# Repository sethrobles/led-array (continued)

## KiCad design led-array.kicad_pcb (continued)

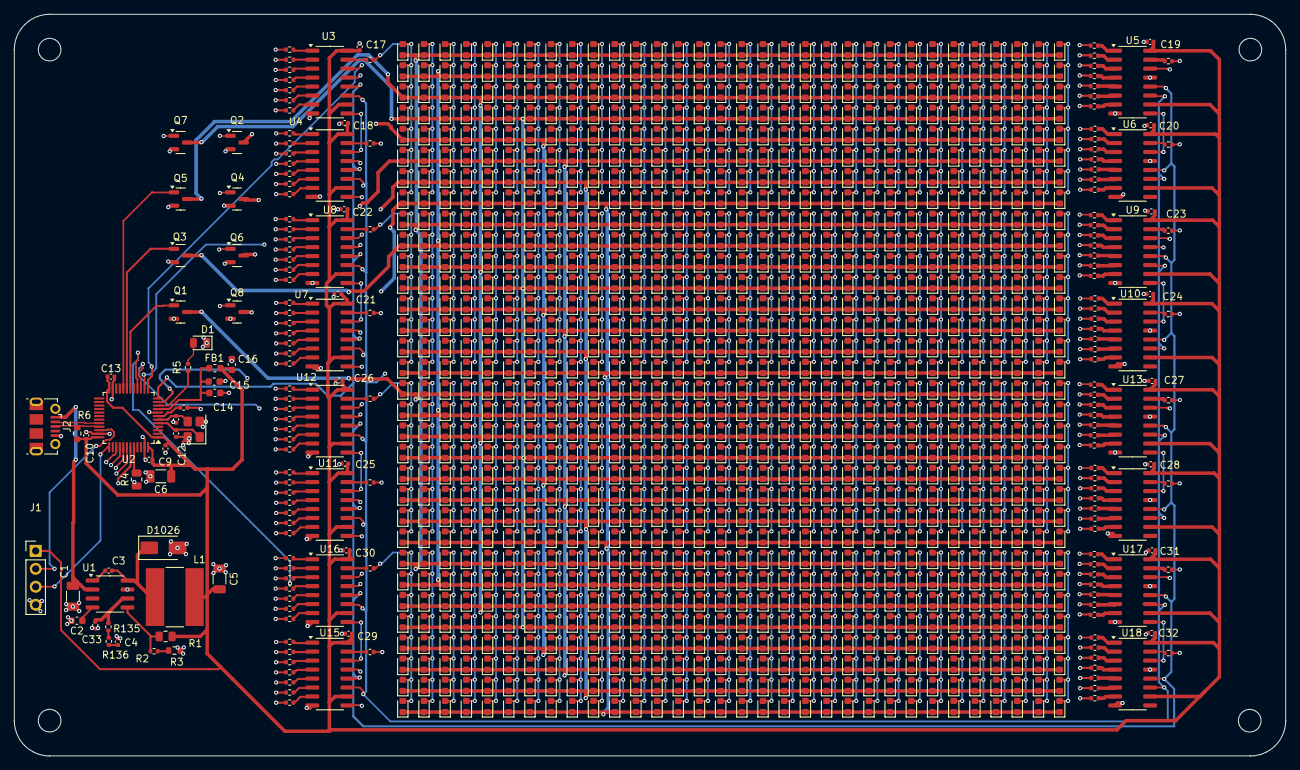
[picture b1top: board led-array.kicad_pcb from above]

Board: 4 copper layers, 180.0 x 105.0 mm, 1230 parts (0 on the bottom side), 312 nets.

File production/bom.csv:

Designator,Footprint,Quantity,Value,LCSC Part #
C1,1206,1,22uF,C12891
"C10, C12, C13, C17, C18, C19, C20, C21, C22, C23, C24, C25, C26, C27, C28, C29, C3, C30, C31, C32, C7, C9",0402,22,100nF,C1525
"C11, C33, C8",0402,3,10pF,C32949
C14,0603,1,10nF,C57112
"C15, C16",0603,2,1uF,C15849 
C2,0603,1,8n2F,C1322360
C4,0402,1,1nF,C1523 
C5,1206,1,100uF,C15008
C6,1206,1,10uF,C13585
D1,0805,1,GREEN_LIGHT,C2297
"D10, D100, D1000, D1001, D1002, D1003, D1004, D1005, D1006, D1007, D1008, D1009, D101, D1010, D1011, D1012, D1013, D1014, D1015, D1016, D1017, D1018, D1019, D102, D1020, D1021, D1022, D1023, D1024, D1025, D103, D104, D105, D106, D107, D108, D109, D11, D110, D111, D112, D113, D114, D115, D116, D117, D118, D119, D12, D120, D121, D122, D123, D124, D125, D126, D127, D128, D129, D13, D130, D131, D132, D133, D134, D135, D136, D137, D138, D139, D14, D140, D141, D142, D143, D144, D145, D146, D147, D148, D149, D15, D150, D151, D152, D153, D154, D155, D156, D157, D158, D159, D16, D160, D161, D162, D163, D164, D165, D166, D167, D168, D169, D17, D170, D171, D172, D173, D174, D175, D176, D177, D178, D179, D18, D180, D181, D182, D183, D184, D185, D186, D187, D188, D189, D19, D190, D191, D192, D193, D194, D195, D196, D197, D198, D199, D2, D20, D200, D201, D202, D203, D204, D205, D206, D207, D208, D209, D21, D210, D211, D212, D213, D214, D215, D216, D217, D218, D219, D22, D220, D221, D222, D223, D224, D225, D226, D227, D228, D229, D23, D230, D231, D232, D233, D234, D235, D236, D237, D238, D239, D24, D240, D241, D242, D243, D244, D245, D246, D247, D248, D249, D25, D250, D251, D252, D253, D254, D255, D256",0603,200,RED,C2286
D1026,D_SMA,1,D_Schottky,C14996
"D257, D258, D259, D26, D260, D261, D262, D263, D264, D265, D266, D267, D268, D269, D27, D270, D271, D272, D273, D274, D275, D276, D277, D278, D279, D28, D280, D281, D282, D283, D284, D285, D286, D287, D288, D289, D29, D290, D291, D292, D293, D294, D295, D296, D297, D298, D299, D3, D30, D300, D301, D302, D303, D304, D305, D306, D307, D308, D309, D31, D310, D311, D312, D313, D314, D315, D316, D317, D318, D319, D32, D320, D321, D322, D323, D324, D325, D326, D327, D328, D329, D33, D330, D331, D332, D333, D334, D335, D336, D337, D338, D339, D34, D340, D341, D342, D343, D344, D345, D346, D347, D348, D349, D35, D350, D351, D352, D353, D354, D355, D356, D357, D358, D359, D36, D360, D361, D362, D363, D364, D365, D366, D367, D368, D369, D37, D370, D371, D372, D373, D374, D375, D376, D377, D378, D379, D38, D380, D381, D382, D383, D384, D385, D386, D387, D388, D389, D39, D390, D391, D392, D393, D394, D395, D396, D397, D398, D399, D4, D40, D400, D401, D402, D403, D404, D405, D406, D407, D408, D409, D41, D410, D411, D412, D413, D414, D415, D416, D417, D418, D419, D42, D420, D421, D422, D423, D424, D425, D426, D427, D428, D429, D43, D430, D431, D432, D433, D434, D435, D436",0603,200,RED,C2286
"D437, D438, D439, D44, D440, D441, D442, D443, D444, D445, D446, D447, D448, D449, D45, D450, D451, D452, D453, D454, D455, D456, D457, D458, D459, D46, D460, D461, D462, D463, D464, D465, D466, D467, D468, D469, D47, D470, D471, D472, D473, D474, D475, D476, D477, D478, D479, D48, D480, D481, D482, D483, D484, D485, D486, D487, D488, D489, D49, D490, D491, D492, D493, D494, D495, D496, D497, D498, D499, D5, D50, D500, D501, D502, D503, D504, D505, D506, D507, D508, D509, D51, D510, D511, D512, D513, D514, D515, D516, D517, D518, D519, D52, D520, D521, D522, D523, D524, D525, D526, D527, D528, D529, D53, D530, D531, D532, D533, D534, D535, D536, D537, D538, D539, D54, D540, D541, D542, D543, D544, D545, D546, D547, D548, D549, D55, D550, D551, D552, D553, D554, D555, D556, D557, D558, D559, D56, D560, D561, D562, D563, D564, D565, D566, D567, D568, D569, D57, D570, D571, D572, D573, D574, D575, D576, D577, D578, D579, D58, D580, D581, D582, D583, D584, D585, D586, D587, D588, D589, D59, D590, D591, D592, D593, D594, D595, D596, D597, D598, D599, D6, D60, D600, D601, D602, D603, D604, D605, D606, D607, D608, D609, D61, D610, D611, D612, D613, D614, D615, D616",0603,200,RED,C2286
"D617, D618, D619, D62, D620, D621, D622, D623, D624, D625, D626, D627, D628, D629, D63, D630, D631, D632, D633, D634, D635, D636, D637, D638, D639, D64, D640, D641, D642, D643, D644, D645, D646, D647, D648, D649, D65, D650, D651, D652, D653, D654, D655, D656, D657, D658, D659, D66, D660, D661, D662, D663, D664, D665, D666, D667, D668, D669, D67, D670, D671, D672, D673, D674, D675, D676, D677, D678, D679, D68, D680, D681, D682, D683, D684, D685, D686, D687, D688, D689, D69, D690, D691, D692, D693, D694, D695, D696, D697, D698, D699, D7, D70, D700, D701, D702, D703, D704, D705, D706, D707, D708, D709, D71, D710, D711, D712, D713, D714, D715, D716, D717, D718, D719, D72, D720, D721, D722, D723, D724, D725, D726, D727, D728, D729, D73, D730, D731, D732, D733, D734, D735, D736, D737, D738, D739, D74, D740, D741, D742, D743, D744, D745, D746, D747, D748, D749, D75, D750, D751, D752, D753, D754, D755, D756, D757, D758, D759, D76, D760, D761, D762, D763, D764, D765, D766, D767, D768, D769, D77, D770, D771, D772, D773, D774, D775, D776, D777, D778, D779, D78, D780, D781, D782, D783, D784, D785, D786, D787, D788, D789, D79, D790, D791, D792, D793, D794, D795, D796, D797",0603,200,RED,C2286
"D798, D799, D8, D80, D800, D801, D802, D803, D804, D805, D806, D807, D808, D809, D81, D810, D811, D812, D813, D814, D815, D816, D817, D818, D819, D82, D820, D821, D822, D823, D824, D825, D826, D827, D828, D829, D83, D830, D831, D832, D833, D834, D835, D836, D837, D838, D839, D84, D840, D841, D842, D843, D844, D845, D846, D847, D848, D849, D85, D850, D851, D852, D853, D854, D855, D856, D857, D858, D859, D86, D860, D861, D862, D863, D864, D865, D866, D867, D868, D869, D87, D870, D871, D872, D873, D874, D875, D876, D877, D878, D879, D88, D880, D881, D882, D883, D884, D885, D886, D887, D888, D889, D89, D890, D891, D892, D893, D894, D895, D896, D897, D898, D899, D9, D90, D900, D901, D902, D903, D904, D905, D906, D907, D908, D909, D91, D910, D911, D912, D913, D914, D915, D916, D917, D918, D919, D92, D920, D921, D922, D923, D924, D925, D926, D927, D928, D929, D93, D930, D931, D932, D933, D934, D935, D936, D937, D938, D939, D94, D940, D941, D942, D943, D944, D945, D946, D947, D948, D949, D95, D950, D951, D952, D953, D954, D955, D956, D957, D958, D959, D96, D960, D961, D962, D963, D964, D965, D966, D967, D968, D969, D97, D970, D971, D972, D973, D974, D975, D976, D977",0603,200,RED,C2286
"D978, D979, D98, D980, D981, D982, D983, D984, D985, D986, D987, D988, D989, D99, D990, D991, D992, D993, D994, D995, D996, D997, D998, D999",0603,24,RED,C2286
FB1,0603,1,120FB,C14709
J1,PinHeader_1x04_P2.54mm_Vertical,1,Conn_01x04_Pin,C5116483
J2,USB_Micro-B_Molex-105017-0001,1,USB_B_Micro,C136000
L1,L_Bourns-SRN8040_8x8.15mm,1,3.6uH,C6496151 
"Q1, Q2, Q3, Q4, Q5, Q6, Q7, Q8",SOT-23,8,Q_NMOS_GDS,C8545 
"R1, R4",0805,2,10k,C17414
"R10, R100, R101, R102, R103, R104, R105, R106, R107, R108, R109, R11, R110, R111, R112, R113, R114, R115, R116, R117, R118, R119, R12, R120, R121, R122, R123, R124, R125, R126, R127, R128, R129, R13, R130, R131, R132, R133, R134, R14, R15, R16, R17, R18, R19, R20, R21, R22, R23, R24, R25, R26, R27, R28, R29, R30, R31, R32, R33, R34, R35, R36, R37, R38, R39, R40, R41, R42, R43, R44, R45, R46, R47, R48, R49, R50, R51, R52, R53, R54, R55, R56, R57, R58, R59, R60, R61, R62, R63, R64, R65, R66, R67, R68, R69, R7, R70, R71, R72, R73, R74, R75, R76, R77, R78, R79, R8, R80, R81, R82, R83, R84, R85, R86, R87, R88, R89, R9, R90, R91, R92, R93, R94, R95, R96, R97, R98, R99",0402,128,200,C25087
R135,0402,1,33k,C25779 
R136,0402,1,3.3k,C25890
R2,0402,1,2k,C4109
R3,0603,1,1k2,C22765
R5,0402,1,470,C25117
R6,0603,1,1k5,C22843
U1,SOIC-8_3.9x4.9mm_P1.27mm,1,TPS54331DR,C9865
"U10, U11, U12, U13, U14, U15, U16, U17, U18, U3, U4, U5, U6, U7, U8, U9",SOIC-16_3.9x9.9mm_P1.27mm,16,74HC595,C5947
U2,LQFP-48_7x7mm_P0.5mm,1,STM32F103C8T6,C8734
Y1,Crystal_SMD_3225-4Pin_3.2x2.5mm,1,16MHz,C9002

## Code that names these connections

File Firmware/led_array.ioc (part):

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Mcu.Name=STM32F103C(8-B)Tx
Mcu.Package=LQFP48
Mcu.UserName=STM32F103C8Tx
PA0-WKUP.GPIOParameters=GPIO_Label
PA0-WKUP.GPIO_Label=Green_LED
PA0-WKUP.Signal=GPIO_Output
PA1.GPIOParameters=GPIO_Label
PA1.GPIO_Label=SRCLK
PA1.Signal=GPIO_Output
PA11.Mode=Device
PA11.Signal=USB_DM
PA12.Mode=Device
PA12.Signal=USB_DP
PA13.Mode=Serial_Wire
PA13.Signal=SYS_JTMS-SWDIO
PA14.Mode=Serial_Wire
PA14.Signal=SYS_JTCK-SWCLK
PA2.GPIOParameters=GPIO_Label
PA2.GPIO_Label=RCLK
PA2.Signal=GPIO_Output
PA3.GPIOParameters=GPIO_Label
PA3.GPIO_Label=SER0
PA3.Signal=GPIO_Output
PA4.GPIOParameters=GPIO_Label
PA4.GPIO_Label=SER1
PA4.Signal=GPIO_Output
PA5.GPIOParameters=GPIO_Label
PA5.GPIO_Label=SER2
PA5.Signal=GPIO_Output
PA6.GPIOParameters=GPIO_Label
PA6.GPIO_Label=SER3
PA6.Signal=GPIO_Output
PB0.GPIOParameters=GPIO_Label
PB0.GPIO_Label=M0
PB0.Signal=GPIO_Output
PB1.GPIOParameters=GPIO_Label
PB1.GPIO_Label=M1
PB1.Signal=GPIO_Output
PB2.GPIOParameters=GPIO_Label
PB2.GPIO_Label=M2
PB2.Signal=GPIO_Output
PB3.GPIOParameters=GPIO_Label
PB3.GPIO_Label=M3
PB3.Signal=GPIO_Output
PB4.GPIOParameters=GPIO_Label
PB4.GPIO_Label=M4
PB4.Signal=GPIO_Output
PB5.GPIOParameters=GPIO_Label
PB5.GPIO_Label=M5
PB5.Signal=GPIO_Output
PB6.GPIOParameters=GPIO_Label
PB6.GPIO_Label=M6
PB6.Signal=GPIO_Output
PB7.GPIOParameters=GPIO_Label
PB7.GPIO_Label=M7
PB7.Signal=GPIO_Output
PD0-OSC_IN.Mode=HSE-External-Oscillator
PD0-OSC_IN.Signal=RCC_OSC_IN
PD1-OSC_OUT.Mode=HSE-External-Oscillator
PD1-OSC_OUT.Signal=RCC_OSC_OUT
RCC.HSEDivPLL=RCC_HSE_PREDIV_DIV2
RCC.HSE_VALUE=16000000
RCC.SYSCLKFreq_VALUE=72000000
RCC.SYSCLKSource=RCC_SYSCLKSOURCE_PLLCLK
board=custom

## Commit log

2025-08-23 Readme
2025-08-23 Redid
2025-09-05 LED updates with some layout
2025-09-05 Updated gitignore
2025-09-16 LEDS wired
2025-09-17 Set up RCLK and SRCLK lines
2025-09-18 Main power and signals wired
2025-09-20 update for miguel
2025-09-26 Relabeled MOSFETs
2025-09-29 Everything wired up
2025-09-29 Actually hopefully final
2025-10-01 PCB laid out
2025-10-13 Updated schematic, still likely need to modify the buck converter
2025-10-18 Modified buck converter in schematic and pcb and got rid of old fabrication files
2025-10-18 Made more edits
2025-10-19 Updated usb-micro, have filled in all LCSC fields
2025-10-19 Modified pins to match JLCPCB layout
2025-12-13 Added firwmare code
2025-12-13 Updated the readme
